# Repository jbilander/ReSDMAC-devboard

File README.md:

# ReSDMAC-devboard
A development board for ReSDMAC

Should be compatible with the [PLCC-84-plug](https://github.com/jbilander/PLCC-84-plug).

***
REV 1A
<br /><br />

<br />

</a>

</a>
<br />

</a>

***

[![CC BY-SA 4.0][cc-by-sa-shield]][cc-by-sa]

This work is licensed under a
[Creative Commons Attribution-ShareAlike 4.0 International License][cc-by-sa].

[![CC BY-SA 4.0][cc-by-sa-image]][cc-by-sa]

[cc-by-sa]: http://creativecommons.org/licenses/by-sa/4.0/
[cc-by-sa-image]: https://licensebuttons.net/l/by-sa/4.0/88x31.png
[cc-by-sa-shield]: https://img.shields.io/badge/License-CC%20BY--SA%204.0-lightgrey.svg

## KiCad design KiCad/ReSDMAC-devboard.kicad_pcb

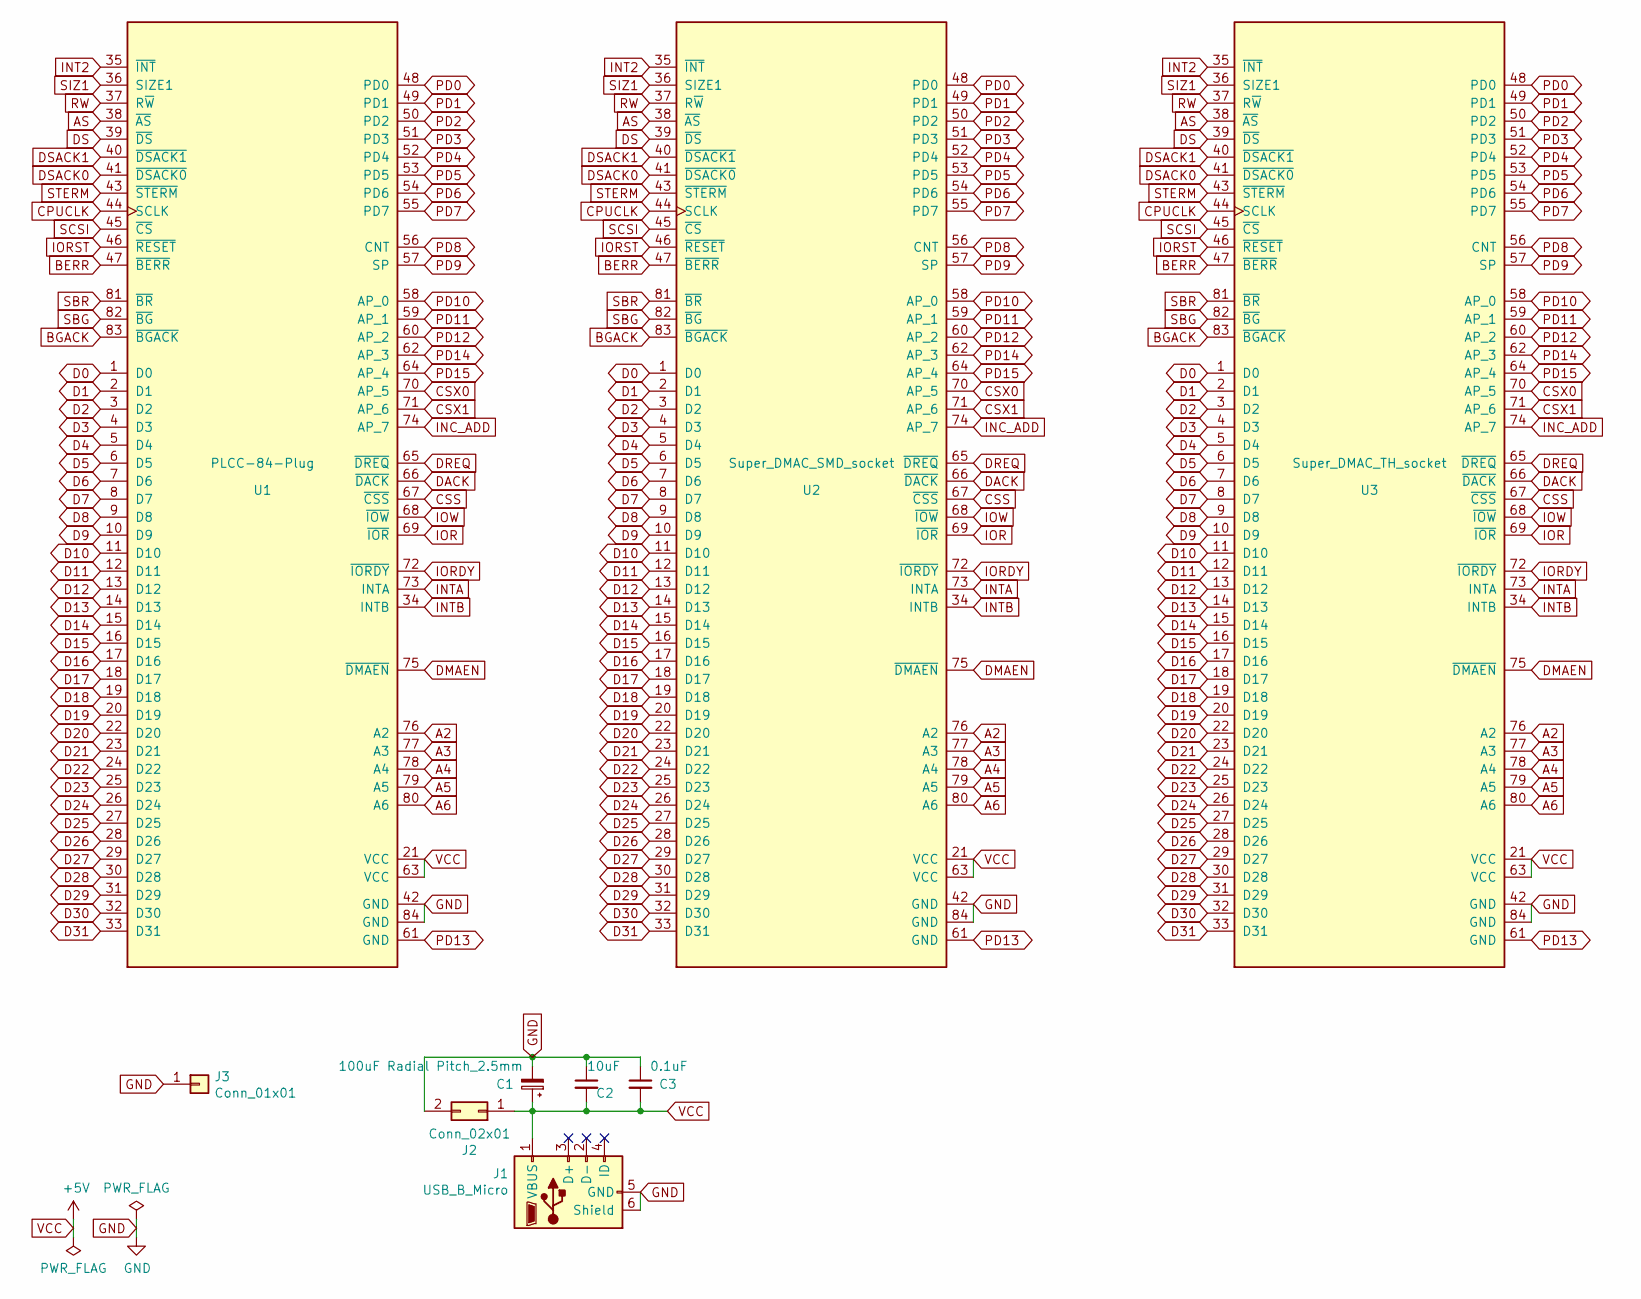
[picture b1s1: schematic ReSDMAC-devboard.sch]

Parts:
C1: 100uF Radial Pitch_2.5mm; CP_Radial_D5.0mm_P2.50mm
C2: 10uF; C_1206_3216Metric_Pad1.33x1.80mm_HandSolder
C3: 0.1uF; C_0805_2012Metric_Pad1.18x1.45mm_HandSolder
J1: USB_B_Micro; USB_Micro-B_Unknown_5s_SMT
J2: Conn_02x01; PinHeader_2x01_P2.54mm_Vertical
J3: Conn_01x01; MountingHole_3.2mm_M3_Pad_Via
U1: PLCC-84-Plug; PLCC-84_Plug_P1.27mm_mirrored
U2: Super_DMAC_SMD_socket; PLCC-84_SMD-Socket_TH_modded
U3: Super_DMAC_TH_socket; PLCC-84_THT-Socket

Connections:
A2: U1.76 (A2), U2.76 (A2), U3.76 (A2)
A3: U1.77 (A3), U2.77 (A3), U3.77 (A3)
A4: U1.78 (A4), U2.78 (A4), U3.78 (A4)
A5: U1.79 (A5), U2.79 (A5), U3.79 (A5)
A6: U1.80 (A6), U2.80 (A6), U3.80 (A6)
AS: U1.38 (~AS), U2.38 (~AS), U3.38 (~AS)
BERR: U1.47 (~BERR), U2.47 (~BERR), U3.47 (~BERR)
BGACK: U1.83 (~BGACK), U2.83 (~BGACK), U3.83 (~BGACK)
CPUCLK: U1.44 (SCLK), U2.44 (SCLK), U3.44 (SCLK)
CSS: U1.67 (~CSS), U2.67 (~CSS), U3.67 (~CSS)
CSX0: U1.70 (AP_5), U2.70 (AP_5), U3.70 (AP_5)
CSX1: U1.71 (AP_6), U2.71 (AP_6), U3.71 (AP_6)
D0: U1.1 (D0), U2.1 (D0), U3.1 (D0)
D1: U1.2 (D1), U2.2 (D1), U3.2 (D1)
D2: U1.3 (D2), U2.3 (D2), U3.3 (D2)
D3: U1.4 (D3), U2.4 (D3), U3.4 (D3)
D4: U1.5 (D4), U2.5 (D4), U3.5 (D4)
D5: U1.6 (D5), U2.6 (D5), U3.6 (D5)
D6: U1.7 (D6), U2.7 (D6), U3.7 (D6)
D7: U1.8 (D7), U2.8 (D7), U3.8 (D7)
D8: U1.9 (D8), U2.9 (D8), U3.9 (D8)
D9: U1.10 (D9), U2.10 (D9), U3.10 (D9)
D10: U1.11 (D10), U2.11 (D10), U3.11 (D10)
D11: U1.12 (D11), U2.12 (D11), U3.12 (D11)
D12: U1.13 (D12), U2.13 (D12), U3.13 (D12)
D13: U1.14 (D13), U2.14 (D13), U3.14 (D13)
D14: U1.15 (D14), U2.15 (D14), U3.15 (D14)
D15: U1.16 (D15), U2.16 (D15), U3.16 (D15)
D16: U1.17 (D16), U2.17 (D16), U3.17 (D16)
D17: U1.18 (D17), U2.18 (D17), U3.18 (D17)
D18: U1.19 (D18), U2.19 (D18), U3.19 (D18)
D19: U1.20 (D19), U2.20 (D19), U3.20 (D19)
D20: U1.22 (D20), U2.22 (D20), U3.22 (D20)
D21: U1.23 (D21), U2.23 (D21), U3.23 (D21)
D22: U1.24 (D22), U2.24 (D22), U3.24 (D22)
D23: U1.25 (D23), U2.25 (D23), U3.25 (D23)
D24: U1.26 (D24), U2.26 (D24), U3.26 (D24)
D25: U1.27 (D25), U2.27 (D25), U3.27 (D25)
D26: U1.28 (D26), U2.28 (D26), U3.28 (D26)
D27: U1.29 (D27), U2.29 (D27), U3.29 (D27)
D28: U1.30 (D28), U2.30 (D28), U3.30 (D28)
D29: U1.31 (D29), U2.31 (D29), U3.31 (D29)
D30: U1.32 (D30), U2.32 (D30), U3.32 (D30)
D31: U1.33 (D31), U2.33 (D31), U3.33 (D31)
DACK: U1.66 (~DACK), U2.66 (~DACK), U3.66 (~DACK)
DMAEN: U1.75 (~DMAEN), U2.75 (~DMAEN), U3.75 (~DMAEN)
DREQ: U1.65 (~DREQ), U2.65 (~DREQ), U3.65 (~DREQ)
DS: U1.39 (~DS), U2.39 (~DS), U3.39 (~DS)
DSACK0: U1.41 (~DSACK0), U2.41 (~DSACK0), U3.41 (~DSACK0)
DSACK1: U1.40 (~DSACK1), U2.40 (~DSACK1), U3.40 (~DSACK1)
GND: C1.2, C2.1, C3.1, J1.5 (GND), J1.6 (Shield), J2.2, J3.1, U1.42 (GND), U1.84 (GND), U2.42 (GND), U2.84 (GND), U3.42 (GND), U3.84 (GND)
INC_ADD: U1.74 (AP_7), U2.74 (AP_7), U3.74 (AP_7)
INT2: U1.35 (~INT), U2.35 (~INT), U3.35 (~INT)
INTA: U1.73 (INTA), U2.73 (INTA), U3.73 (INTA)
INTB: U1.34 (INTB), U2.34 (INTB), U3.34 (INTB)
IOR: U1.69 (~IOR), U2.69 (~IOR), U3.69 (~IOR)
IORDY: U1.72 (~IORDY), U2.72 (~IORDY), U3.72 (~IORDY)
IORST: U1.46 (~RESET), U2.46 (~RESET), U3.46 (~RESET)
IOW: U1.68 (~IOW), U2.68 (~IOW), U3.68 (~IOW)
PD0: U1.48 (PD0), U2.48 (PD0), U3.48 (PD0)
PD1: U1.49 (PD1), U2.49 (PD1), U3.49 (PD1)
PD2: U1.50 (PD2), U2.50 (PD2), U3.50 (PD2)
PD3: U1.51 (PD3), U2.51 (PD3), U3.51 (PD3)
PD4: U1.52 (PD4), U2.52 (PD4), U3.52 (PD4)
PD5: U1.53 (PD5), U2.53 (PD5), U3.53 (PD5)
PD6: U1.54 (PD6), U2.54 (PD6), U3.54 (PD6)
PD7: U1.55 (PD7), U2.55 (PD7), U3.55 (PD7)
PD8: U1.56 (CNT), U2.56 (CNT), U3.56 (CNT)
PD9: U1.57 (SP), U2.57 (SP), U3.57 (SP)
PD10: U1.58 (AP_0), U2.58 (AP_0), U3.58 (AP_0)
PD11: U1.59 (AP_1), U2.59 (AP_1), U3.59 (AP_1)
PD12: U1.60 (AP_2), U2.60 (AP_2), U3.60 (AP_2)
PD13: U1.61 (GND), U2.61 (GND), U3.61 (GND)
PD14: U1.62 (AP_3), U2.62 (AP_3), U3.62 (AP_3)
PD15: U1.64 (AP_4), U2.64 (AP_4), U3.64 (AP_4)
RW: U1.37 (R~W), U2.37 (R~W), U3.37 (R~W)
SBG: U1.82 (~BG), U2.82 (~BG), U3.82 (~BG)
SBR: U1.81 (~BR), U2.81 (~BR), U3.81 (~BR)
SCSI: U1.45 (~CS), U2.45 (~CS), U3.45 (~CS)
SIZ1: U1.36 (SIZE1), U2.36 (SIZE1), U3.36 (SIZE1)
STERM: U1.43 (~STERM), U2.43 (~STERM), U3.43 (~STERM)
VCC: C1.1, C2.2, C3.2, J1.1 (VBUS), J2.1, U1.21 (VCC), U1.63 (VCC), U2.21 (VCC), U2.63 (VCC), U3.21 (VCC), U3.63 (VCC)

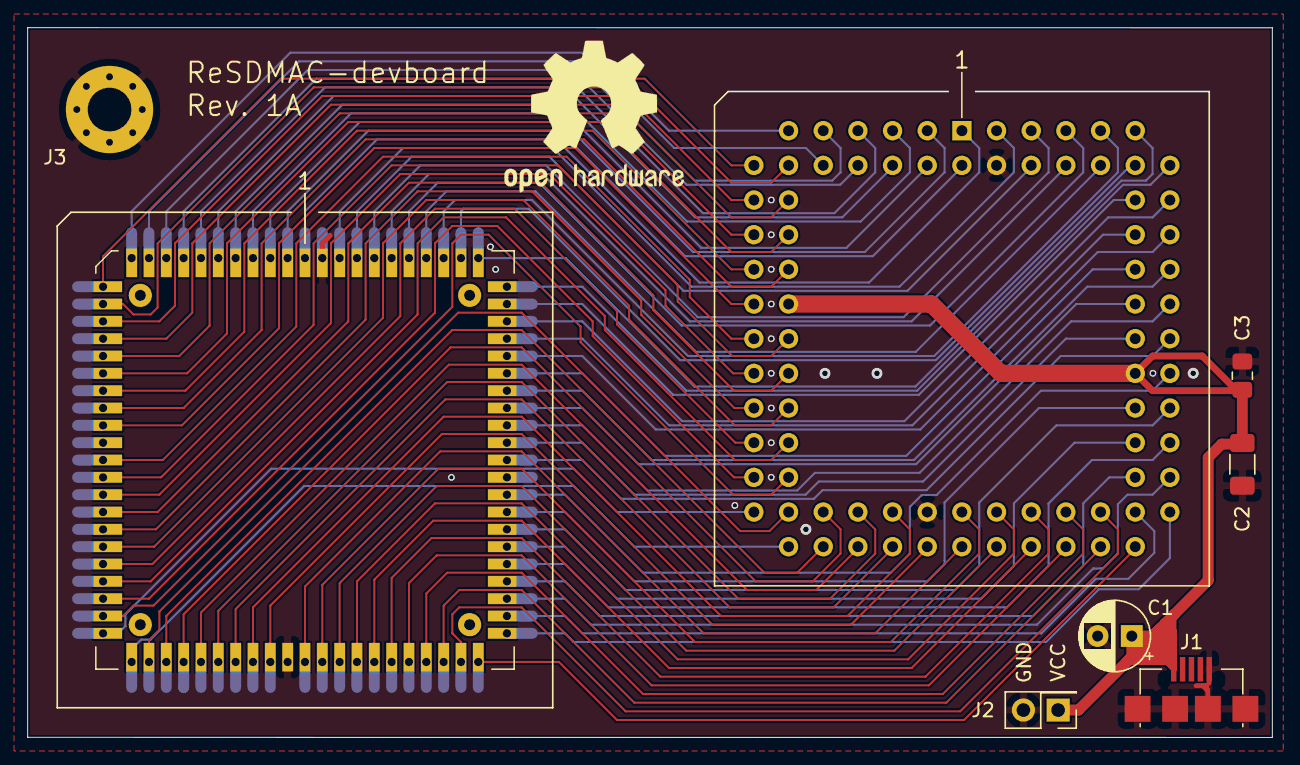
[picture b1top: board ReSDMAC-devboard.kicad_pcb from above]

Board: 4 copper layers, 91.2 x 52.0 mm, 9 parts (1 on the bottom side), 82 nets.

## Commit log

2024-04-25 Create LICENSE
2024-04-25 Add footprints
2024-04-25 Add files
2024-04-25 Added nets and started routing
2024-04-26 Routing of all traces done
2024-04-26 Fixed caps and power circuit routing
2024-04-26 Added MountingHole_3.2mm_M3_Pad_Via for grounding wire with ring lug connector
2024-04-27 small routing fix, only cosmetic
2024-04-27 Add images
2024-04-27 Add schematic pdf
